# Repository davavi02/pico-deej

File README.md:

# pico-deej
This verison of the project uses a RP2040 Zero and a 74HC4051D multiplexer to get 5 sliders at a time.

## BOM
| Part | Qty. | Link |
|------|------|------|
| RP2040 Zero | 1 | [Amazon](https://a.co/d/6Iz0y2I)
| Nexperia 74HC4051D | 1 | [Mouser](https://www.mouser.com/ProductDetail/771-74HC4051D-T) |
| TT Electronics PS45M-0MC1BR500K | 5 | [Mouser](https://www.mouser.com/ProductDetail/858-PS45M-0MC1BR500K) |

## CAD/PCB
STL files for a case are included and source files are also included for modifications in FreeCAD. First attempt at creating a PCB is also included, designed in KiCAD 

## Firmware
The MCU code is also included which was modified to handle a multiplexer. The code is using the sample code from [SparkFun's multiplexer hookup guide](https://learn.sparkfun.com/tutorials/multiplexer-breakout-hookup-guide/all).

# Original Readme

deej is an **open-source hardware volume mixer** for Windows and Linux PCs. It lets you use real-life sliders (like a DJ!) to **seamlessly control the volumes of different apps** (such as your music player, the game you're playing and your voice chat session) without having to stop what you're doing.

**Join the [deej Discord server](https://discord.gg/nf88NJu) if you need help or have any questions!**

> **_New:_** [work-in-progress deej FAQ](./docs/faq/faq.md)!

deej consists of a [lightweight desktop client](#features) written in Go, and an Arduino-based hardware setup that's simple and cheap to build. [**Check out some versions built by members of our community!**](./community.md)

**[Download the latest release](https://github.com/omriharel/deej/releases/latest) | [Video demonstration](https://youtu.be/VoByJ4USMr8) | [Build video by Tech Always](https://youtu.be/x2yXbFiiAeI)**

> _**Psst!** [No 3D printer? No problem!](./assets/build-shoebox.jpg)_ You can build deej on some cardboard, a shoebox or even a breadboard :)

## Table of contents

- [Features](#features)
- [How it works](#how-it-works)
  - [Hardware](#hardware)
    - [Schematic](#schematic)
  - [Software](#software)
- [Slider mapping (configuration)](#slider-mapping-configuration)
- [Build your own!](#build-your-own)
  - [FAQ](#faq)
  - [Build video](#build-video)
  - [Bill of Materials](#bill-of-materials)
  - [Thingiverse collection](#thingiverse-collection)
  - [Build procedure](#build-procedure)
- [How to run](#how-to-run)
  - [Requirements](#requirements)
  - [Download and installation](#download-and-installation)
  - [Building from source](#building-from-source)
- [Community](#community)
- [License](#license)

## Features

deej is written in Go and [distributed](https://github.com/omriharel/deej/releases/latest) as a portable (no installer needed) executable.

- Bind apps to different sliders
  - Bind multiple apps per slider (i.e. one slider for all your games)
  - Bind the master channel
  - Bind "system sounds" (on Windows)
  - Bind specific audio devices by name (on Windows)
  - Bind currently active app (on Windows)
  - Bind all other unassigned apps
- Control your microphone's input level
- Lightweight desktop client, consuming around 10MB of memory
- Runs from your system tray
- Helpful notifications to let you know if something isn't working

> **Looking for the older Python version?** It's no longer maintained, but you can always find it in the [`legacy-python` branch](https://github.com/omriharel/deej/tree/legacy-python).

## How it works

### Hardware

- The sliders are connected to 5 (or as many as you like) analog pins on an Arduino Nano/Uno board. They're powered from the board's 5V output (see schematic)
- The board connects via a USB cable to the PC

#### Schematic

### Software

- The code running on the Arduino board is a [C program](./arduino/deej-5-sliders-vanilla/deej-5-sliders-vanilla.ino) constantly writing current slider values over its serial interface
- The PC runs a lightweight [Go client](./pkg/deej/cmd/main.go) in the background. This client reads the serial stream and adjusts app volumes according to the given configuration file

## Slider mapping (configuration)

deej uses a simple YAML-formatted configuration file named [`config.yaml`](./config.yaml), placed alongside the deej executable.

The config file determines which applications (and devices) are mapped to which sliders, and which parameters to use for the connection to the Arduino board, as well as other user preferences.

**This file auto-reloads when its contents are changed, so you can change application mappings on-the-fly without restarting deej.**

It looks like this:

```yaml
slider_mapping:
  0: master
  1: chrome.exe
  2: spotify.exe
  3:
    - pathofexile_x64.exe
    - rocketleague.exe
  4: discord.exe

# set this to true if you want the controls inverted (i.e. top is 0%, bottom is 100%)
invert_sliders: false

# settings for connecting to the arduino board
com_port: COM4
baud_rate: 9600

# adjust the amount of signal noise reduction depending on your hardware quality
# supported values are "low" (excellent hardware), "default" (regular hardware) or "high" (bad, noisy hardware)
noise_reduction: default
```

- `master` is a special option to control the master volume of the system _(uses the default playback device)_
- `mic` is a special option to control your microphone's input level _(uses the default recording device)_
- `deej.unmapped` is a special option to control all apps that aren't bound to any slider ("everything else")
- On Windows, `deej.current` is a special option to control whichever app is currently in focus
- On Windows, you can specify a device's full name, i.e. `Speakers (Realtek High Definition Audio)`, to bind that device's level to a slider. This doesn't conflict with the default `master` and `mic` options, and works for both input and output devices.
  - Be sure to use the full device name, as seen in the menu that comes up when left-clicking the speaker icon in the tray menu
- `system` is a special option on Windows to control the "System sounds" volume in the Windows mixer
- All names are case-**in**sensitive, meaning both `chrome.exe` and `CHROME.exe` will work
- You can create groups of process names (using a list) to either:
    - control more than one app with a single slider
    - choose whichever process in the group that's currently running (i.e. to have one slider control any game you're playing)

## Build your own!

Building deej is very simple. You only need a few relatively cheap parts - it's an excellent starter project (and my first Arduino project, personally). Remember that if you need any help or have a question that's not answered here, you can always [join the deej Discord server](https://discord.gg/nf88NJu).

Build deej for yourself, or as an awesome gift for your gaming buddies!

### FAQ

I've started a highly focused effort of writing a proper FAQ page for deej, covering many basic and advanced topics.

It is still _very much a work-in-progress_, but I'm happy to [share it in its current state](./docs/faq/faq.md) in hopes that it at least covers some questions you might have.

FAQ feedback in our [community Discord](https://discord.gg/nf88NJu) is strongly encouraged :)

### Build video

In case you prefer watching to reading, Charles from the [**Tech Always**](https://www.youtube.com/c/TechAlways) YouTube channel has made [**a fantastic video**](https://youtu.be/x2yXbFiiAeI) that covers the basics of building deej for yourself, including parts, costs, assembly and software. I highly recommend checking it out!

### Bill of Materials

- An Arduino Nano, Pro Micro or Uno board
  - I officially recommend using a Nano or a Pro Micro for their smaller form-factor, friendlier USB connectors and more analog pins. Plus they're cheaper
  - You can also use any other development board that has a Serial over USB interface
- A few slider potentiometers, up to your number of free analog pins (the cheaper ones cost around 1-2 USD each, and come with a standard 10K Ohm variable resistor. These _should_ work just fine for this project)
  - **Important:** make sure to get **linear** sliders, not logarithmic ones! Check the product description
  - You can also use circular knobs if you like
- Some wires
- Any kind of box to hold everything together. **You don't need a 3D printer for this project!** It works fantastically with just a piece of cardboard or a shoebox. That being said, if you do have one, read on...

### Thingiverse collection

With many different 3D-printed designs being added to our [community showcase](./community.md), it felt right to gather all of them in a Thingiverse collection for you to browse. If you have access to a 3D printer, feel free to use one of the designs in your build.

**[Visit our community-created design collection on Thingiverse!](https://thingiverse.com/omriharel/collections/deej)**

> You can also [submit your own](https://discord.gg/nf88NJu) design to be added to the collection. Regardless, if you do upload your design to Thingiverse, _please add a `deej` tag to it so that others can find it more easily_.

### Build procedure

- Connect everything according to the [schematic](#schematic)
- Test with a multimeter to be sure your sliders are hooked up correctly
- Flash the Arduino chip with the sketch in [`arduino\deej-5-sliders-vanilla`](./arduino/deej-5-sliders-vanilla/deej-5-sliders-vanilla.ino)
  - _Important:_ If you have more or less than 5 sliders, you must edit the sketch to match what you have
- After flashing, check the serial monitor. You should see a constant stream of values separated by a pipe (`|`) character, e.g. `0|240|1023|0|483`
  - When you move a slider, its corresponding value should move between 0 and 1023
- Congratulations, you're now ready to run the deej executable!

## How to run

### Requirements

#### Windows

- Windows. That's it

#### Linux

- Install `libgtk-3-dev`, `libappindicator3-dev` and `libwebkit2gtk-4.0-dev` for system tray support. Pre-built Linux binaries aren't currently released, so you'll need to [build from source](#building-from-source). If there's demand for pre-built binaries, please [let me know](https://discord.gg/nf88NJu)!

### Download and installation

- Head over to the [releases page](https://github.com/omriharel/deej/releases) and download the [latest version](https://github.com/omriharel/deej/releases/latest)'s executable and configuration file (`deej.exe` and `config.yaml`)
- Place them in the same directory anywhere on your machine
- (Optional, on Windows) Create a shortcut to `deej.exe` and copy it to `%APPDATA%\Microsoft\Windows\Start Menu\Programs\Startup` to have deej run on boot

### Building from source

If you'd rather not download a compiled executable, or want to extend deej or modify it to your needs, feel free to clone the repository and build it yourself. All you need is a Go 1.14 (or above) environment on your machine. If you go this route, make sure to check out the [developer scripts](./pkg/deej/scripts).

Like other Go packages, you can also use the `go get` tool: `go get -u github.com/omriharel/deej`. Please note that the package code now resides in the `pkg/deej` directory, and needs to be imported from there if used inside another project.

If you need any help with this, please [join our Discord server](https://discord.gg/nf88NJu).

## Community

deej is a relatively new project, but a vibrant and awesome community is rapidly growing around it. Come hang out with us in the [deej Discord server](https://discord.gg/nf88NJu), or check out a whole bunch of cool and creative builds made by our members in the [community showcase](./community.md).

The server is also a great place to ask questions, suggest features or report bugs (but of course, feel free to use GitHub if you prefer).

### Donations

If you love deej and want to show your support for this project, you can do so using the link below. Please don't feel obligated to donate - building the project and telling your friends about it goes a very long way! Thank you very much.

### Contributing

Please see [`docs/CONTRIBUTING.md`](./docs/CONTRIBUTING.md).

## License

deej is released under the [MIT license](./LICENSE).

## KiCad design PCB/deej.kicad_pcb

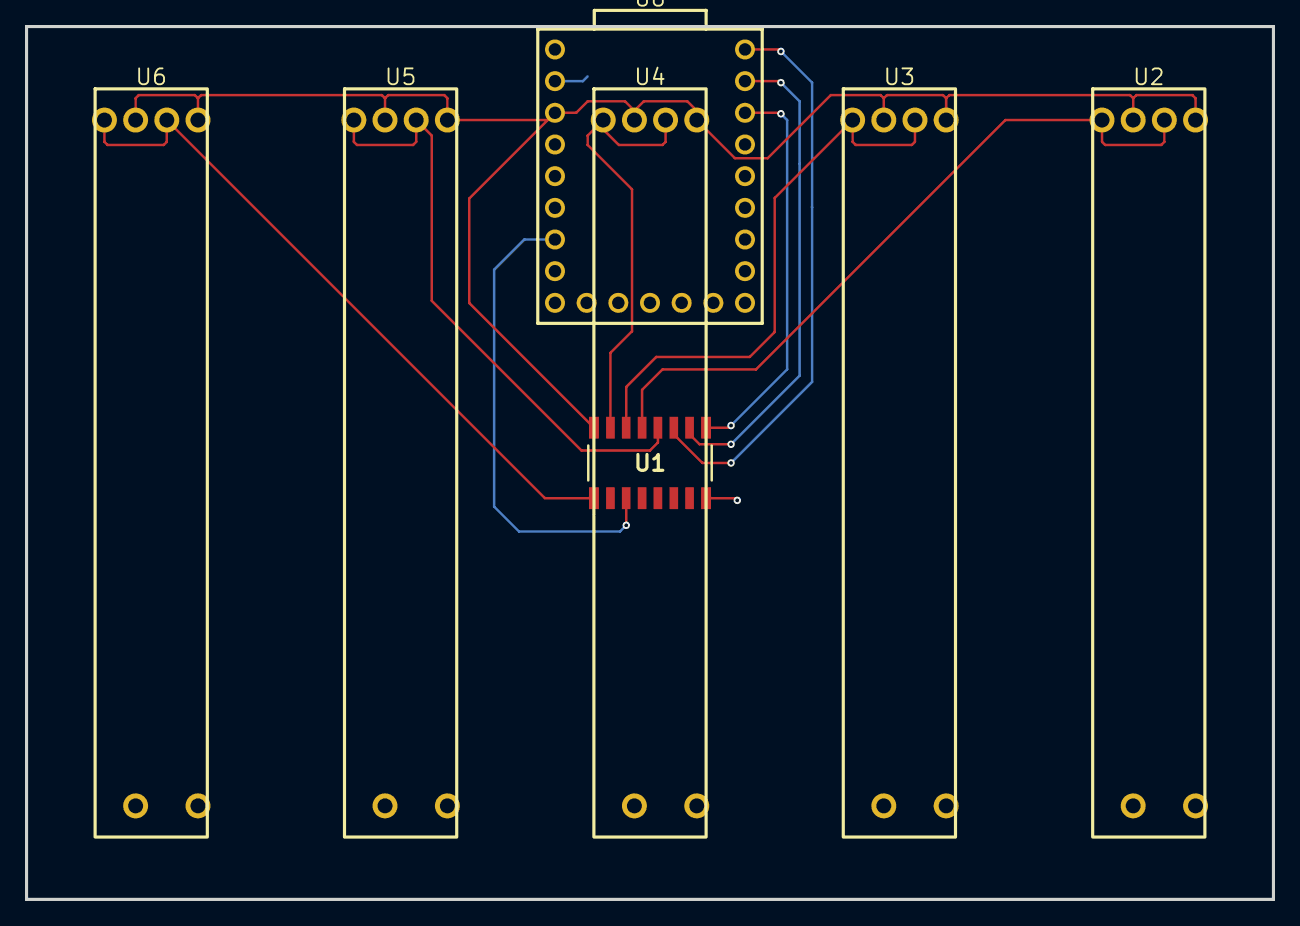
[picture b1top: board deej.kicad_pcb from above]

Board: 2 copper layers, 100.0 x 70.0 mm, 7 parts (0 on the bottom side), 11 nets.

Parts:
U1: 74HC4051; 74HC4051D653
U2, U3, U4, U5, U6: PS45M-0MC1BR500K
U8: RP2040-ZERO; TH_RP2040-ZERO

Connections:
GND: U1.8 (GND), U2.3 (GND1), U2.6 (GND2), U3.3 (GND1), U3.6 (GND2), U4.3 (GND1), U4.6 (GND2), U5.3 (GND1), U5.6 (GND2), U6.3 (GND1), U6.6 (GND2), U8.22 (GND)
unnamed: U1.11 (S0), U8.1 (GP0)
unnamed: U1.10 (S1), U8.2 (GP1)
unnamed: U1.9 (S2), U8.3 (GP2)
unnamed: U1.13 (Y0), U2.1 (OUT1), U2.4 (OUT2)
unnamed: U1.14 (Y1), U3.1 (OUT1), U3.4 (OUT2)
unnamed: U1.15 (Y2), U4.1 (OUT1), U4.4 (OUT2)
unnamed: U1.12 (Y3), U5.1 (OUT1), U5.4 (OUT2)
unnamed: U1.1 (Y4), U6.1 (OUT1), U6.4 (OUT2)
unnamed: U1.3 (Z), U8.17 (GP26)
VCC: U1.16 (VCC), U2.2 (VCC1), U2.5 (VCC2), U3.2 (VCC1), U3.5 (VCC2), U4.2 (VCC1), U4.5 (VCC2), U5.2 (VCC1), U5.5 (VCC2), U6.2 (VCC1), U6.5 (VCC2), U8.21 (3V3)

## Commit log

2026-01-30 Added project files
